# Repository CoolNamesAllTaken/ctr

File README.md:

# ctr

## Software
The data model supports the scenario where N (2, currently) train cars make
scheduled runs northbound (towards San Francisco) and southbound (towards San
Jose).
Riders tap NFC Chipper Cards on and off at station kiosks, and are charged by zone. Live delays will be computed by on-train GPS, and service alerts will explain them.

The code lives in [`website/`](website/): a Django API (Django Ninja,
Postgres) and a Next.js frontend. See [`website/README.md`](website/README.md)
for setup, and
[`website/backend/core/models.py`](website/backend/core/models.py) for the data
model.

The train's Raspberry Pi runs the light and sound controls at
http://caltreat.local:8080/. That code lives in [`pi/`](pi/). See
[`pi/README.md`](pi/README.md) for how to deploy it.

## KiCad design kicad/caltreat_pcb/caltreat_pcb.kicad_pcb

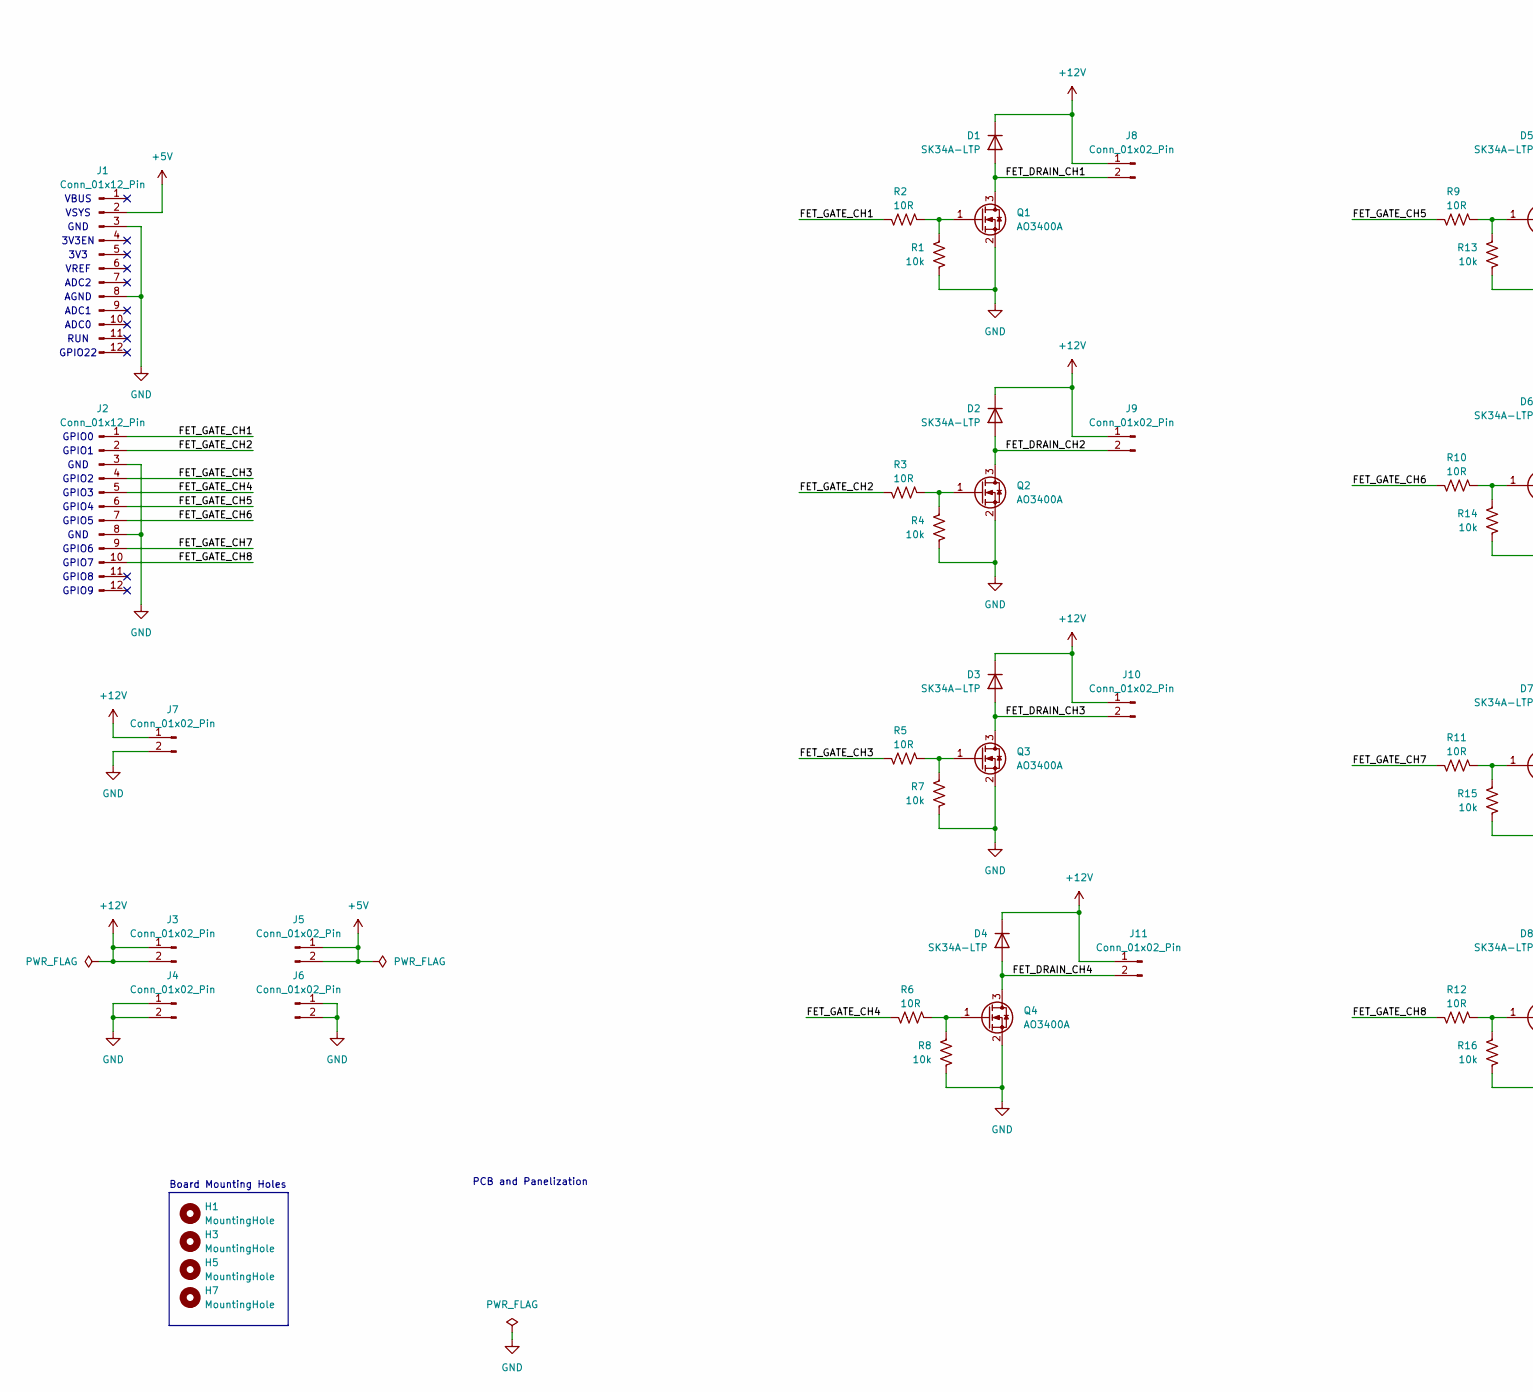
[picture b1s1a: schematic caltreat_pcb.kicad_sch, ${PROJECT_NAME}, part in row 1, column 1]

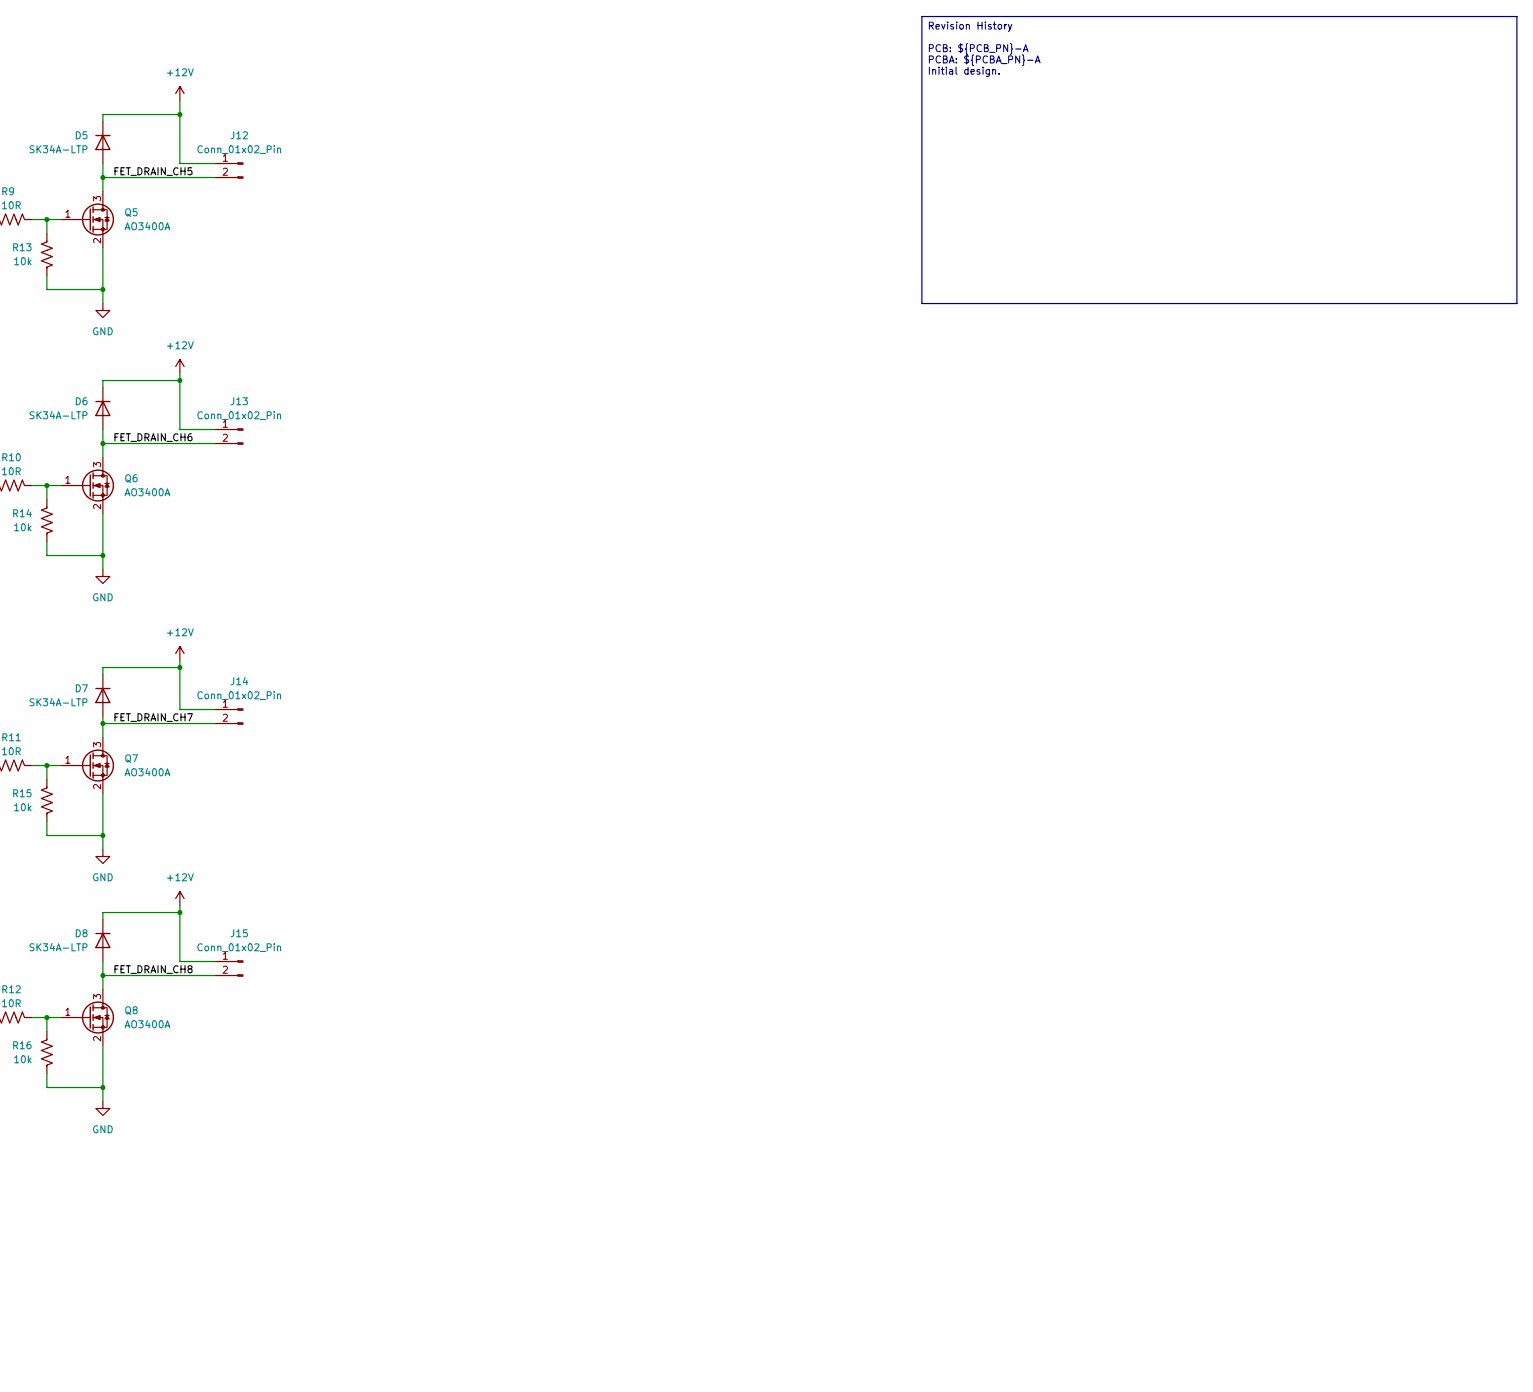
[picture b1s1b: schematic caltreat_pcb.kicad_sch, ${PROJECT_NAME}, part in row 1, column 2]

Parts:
D1, D2, D3, D4, D5, D6, D7, D8: SK34A-LTP; D_SMA
H1, H3, H5, H7: MountingHole; MountingHole_2.7mm_M2.5_Isolated
J1, J2: Conn_01x12_Pin; PinHeader_1x12_P2.54mm_Vertical
J3, J4, J5, J6: Conn_01x02_Pin; PinHeader_1x02_P2.54mm_Vertical
J7, J8, J9, J10, J11, J12, J13, J14, J15: Conn_01x02_Pin; TerminalBlock_Phoenix_MKDS-1-2-3.81_1x02_P3.81mm_Horizontal
Q1, Q2, Q3, Q4, Q5, Q6, Q7, Q8: AO3400A; SOT-23_Handsoldering
R1, R4, R7, R8, R13, R14, R15, R16: 10k; R_0805_2012Metric_Pad1.20x1.40mm_HandSolder
R2, R3, R5, R6, R9, R10, R11, R12: 10R; R_0805_2012Metric_Pad1.20x1.40mm_HandSolder

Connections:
+5V: J1.2, J5.1, J5.2
+12V: D1.1 (K), D2.1 (K), D3.1 (K), D4.1 (K), D5.1 (K), D6.1 (K), D7.1 (K), D8.1 (K), J3.1, J3.2, J7.1, J8.1, J9.1, J10.1, J11.1, J12.1, J13.1, J14.1, J15.1
/FET_DRAIN_CH1: D1.2 (A), J8.2, Q1.3 (D)
/FET_DRAIN_CH2: D2.2 (A), J9.2, Q2.3 (D)
/FET_DRAIN_CH3: D3.2 (A), J10.2, Q3.3 (D)
/FET_DRAIN_CH4: D4.2 (A), J11.2, Q4.3 (D)
/FET_DRAIN_CH5: D5.2 (A), J12.2, Q5.3 (D)
/FET_DRAIN_CH6: D6.2 (A), J13.2, Q6.3 (D)
/FET_DRAIN_CH7: D7.2 (A), J14.2, Q7.3 (D)
/FET_DRAIN_CH8: D8.2 (A), J15.2, Q8.3 (D)
/FET_GATE_CH1: J2.1, R2.1
/FET_GATE_CH2: J2.2, R3.1
/FET_GATE_CH3: J2.4, R5.1
/FET_GATE_CH4: J2.5, R6.1
/FET_GATE_CH5: J2.6, R9.1
/FET_GATE_CH6: J2.7, R10.1
/FET_GATE_CH7: J2.9, R11.1
/FET_GATE_CH8: J2.10, R12.1
GND: J1.3, J1.8, J2.3, J2.8, J4.1, J4.2, J6.1, J6.2, J7.2, Q1.2 (S), Q2.2 (S), Q3.2 (S), Q4.2 (S), Q5.2 (S), Q6.2 (S), Q7.2 (S), Q8.2 (S), R1.2, R4.2, R7.2, R8.2, R13.2, R14.2, R15.2, R16.2
unnamed: Q1.1 (G), R1.1, R2.2
unnamed: Q2.1 (G), R3.2, R4.1
unnamed: Q3.1 (G), R5.2, R7.1
unnamed: Q4.1 (G), R6.2, R8.1
unnamed: Q5.1 (G), R9.2, R13.1
unnamed: Q6.1 (G), R10.2, R14.1
unnamed: Q7.1 (G), R11.2, R15.1
unnamed: Q8.1 (G), R12.2, R16.1

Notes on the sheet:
VSYS
GPIO6
GPIO2
GPIO5
GND
GPIO9
GPIO8
3V3
AGND
RUN
3V3EN
ADC2
GPIO1
GPIO22
ADC0
VBUS
GPIO7
VREF
PCB and Panelization
GPIO0
Board Mounting Holes
GPIO3
ADC1
GPIO4
Revision History PCB: ${PCB_PN}-A PCBA: ${PCBA_PN}-A Initial design.

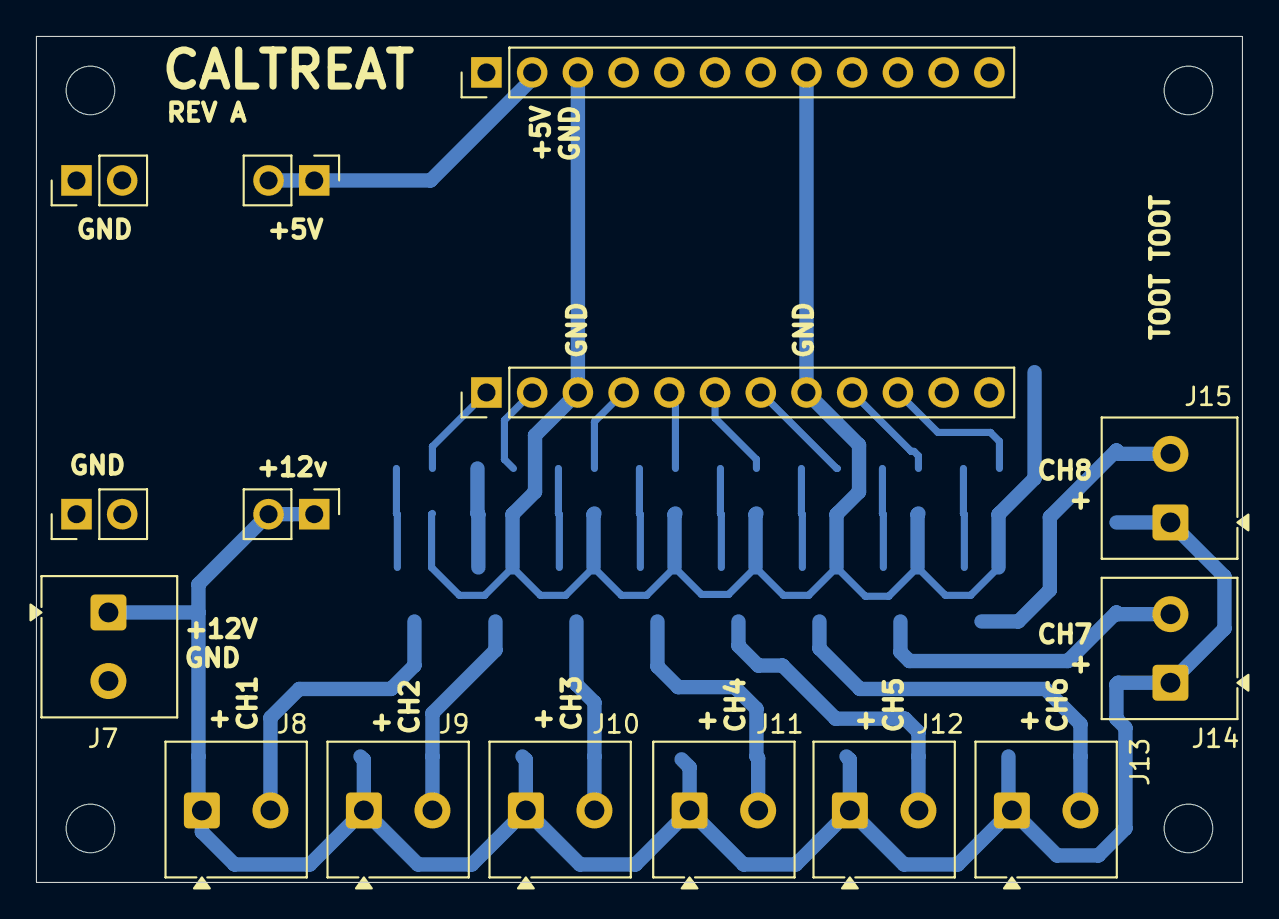
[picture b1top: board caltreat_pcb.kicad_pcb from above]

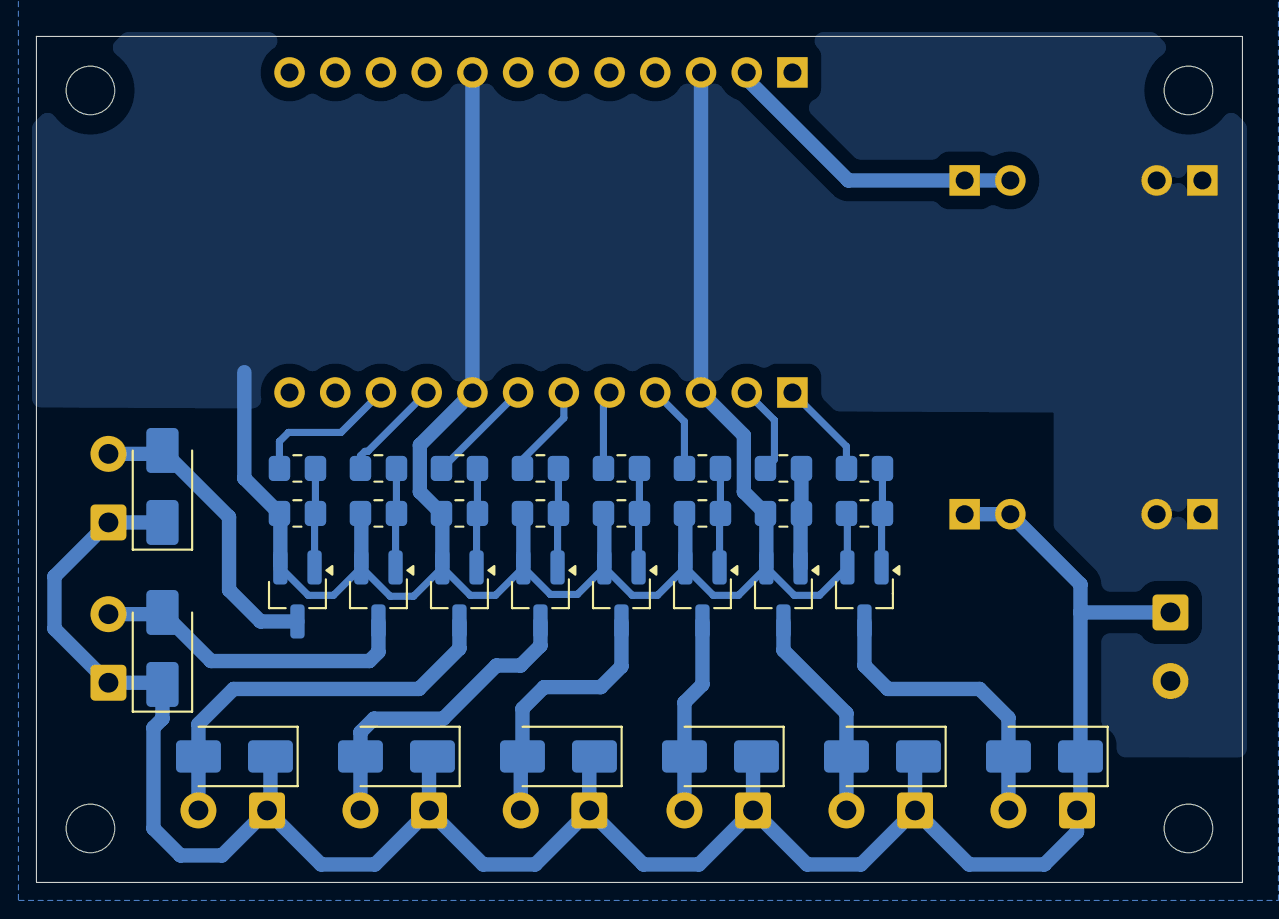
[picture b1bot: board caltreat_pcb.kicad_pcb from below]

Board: 2 copper layers, 67.0 x 47.0 mm, 51 parts (32 on the bottom side), 27 nets.
